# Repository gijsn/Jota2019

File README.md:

# Jota2019
Dit is het bordje van Jota2019 van Scoutinggroep Wielewaal

Er zijn verschillende versies beschikbaar

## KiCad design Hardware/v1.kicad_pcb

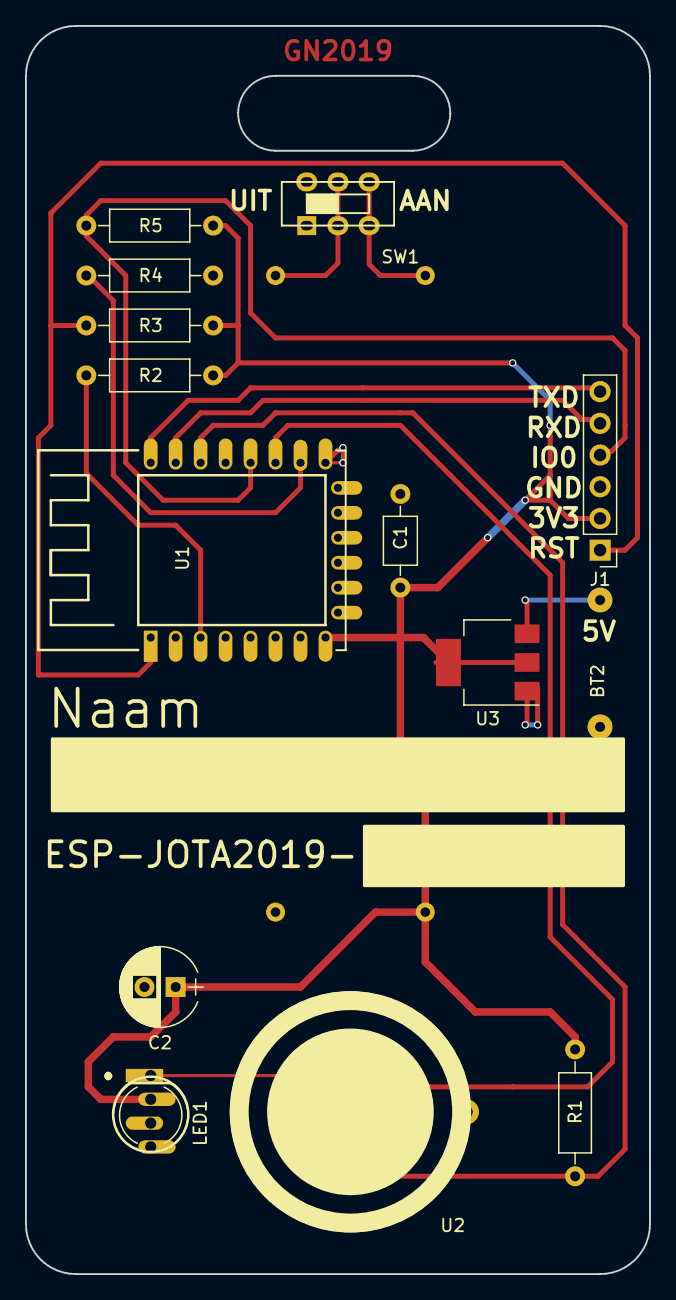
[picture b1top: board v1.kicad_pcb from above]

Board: 2 copper layers, 50.0 x 100.0 mm, 15 parts (1 on the bottom side), 13 nets.

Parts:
BT1: Battery_holder; AA_battery_holder
BT2: Battery; WireConnection_0.80mmDrill
C1: 100nF; C_Axial_L3.8mm_D2.6mm_P7.50mm_Horizontal
C2: 100uF; CP_Radial_D6.3mm_P2.50mm
J1: CONN_01X06; Socket_Strip_Straight_1x06_Pitch2.54mm
LED1: WS2812B; apa106
R1, R2, R3, R4, R5: 10K; R_Axial_DIN0207_L6.3mm_D2.5mm_P10.16mm_Horizontal
SW1: SW_DPDT_x2; Switch
U1: ESP-12E
U2: iButton_reader
U3: AP111733; SOT-223

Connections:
1Wire: R1.2, U1.14, U2.1
+3V3: BT1.1, C1.1, C2.1, J1.2, LED1.2, R1.1, R2.1, R3.1, R5.1, U1.8, U3.2, U3.4
+5V: BT2.1, U3.3
GND: BT1.4, BT2.2, C1.2, C2.2, J1.3, LED1.3, R4.1, U1.9, U2.2, U3.1
GPIO0: J1.4, R5.2, U1.12
unnamed: BT1.2, SW1.3, SW1.6
unnamed: BT1.3, SW1.2, SW1.5
unnamed: R2.2, U1.3
unnamed: R4.2, U1.10
RESET: J1.1, R3.2, U1.1
RGBLED: LED1.1, U1.11
RX: J1.5, U1.15
TX: J1.6, U1.16
